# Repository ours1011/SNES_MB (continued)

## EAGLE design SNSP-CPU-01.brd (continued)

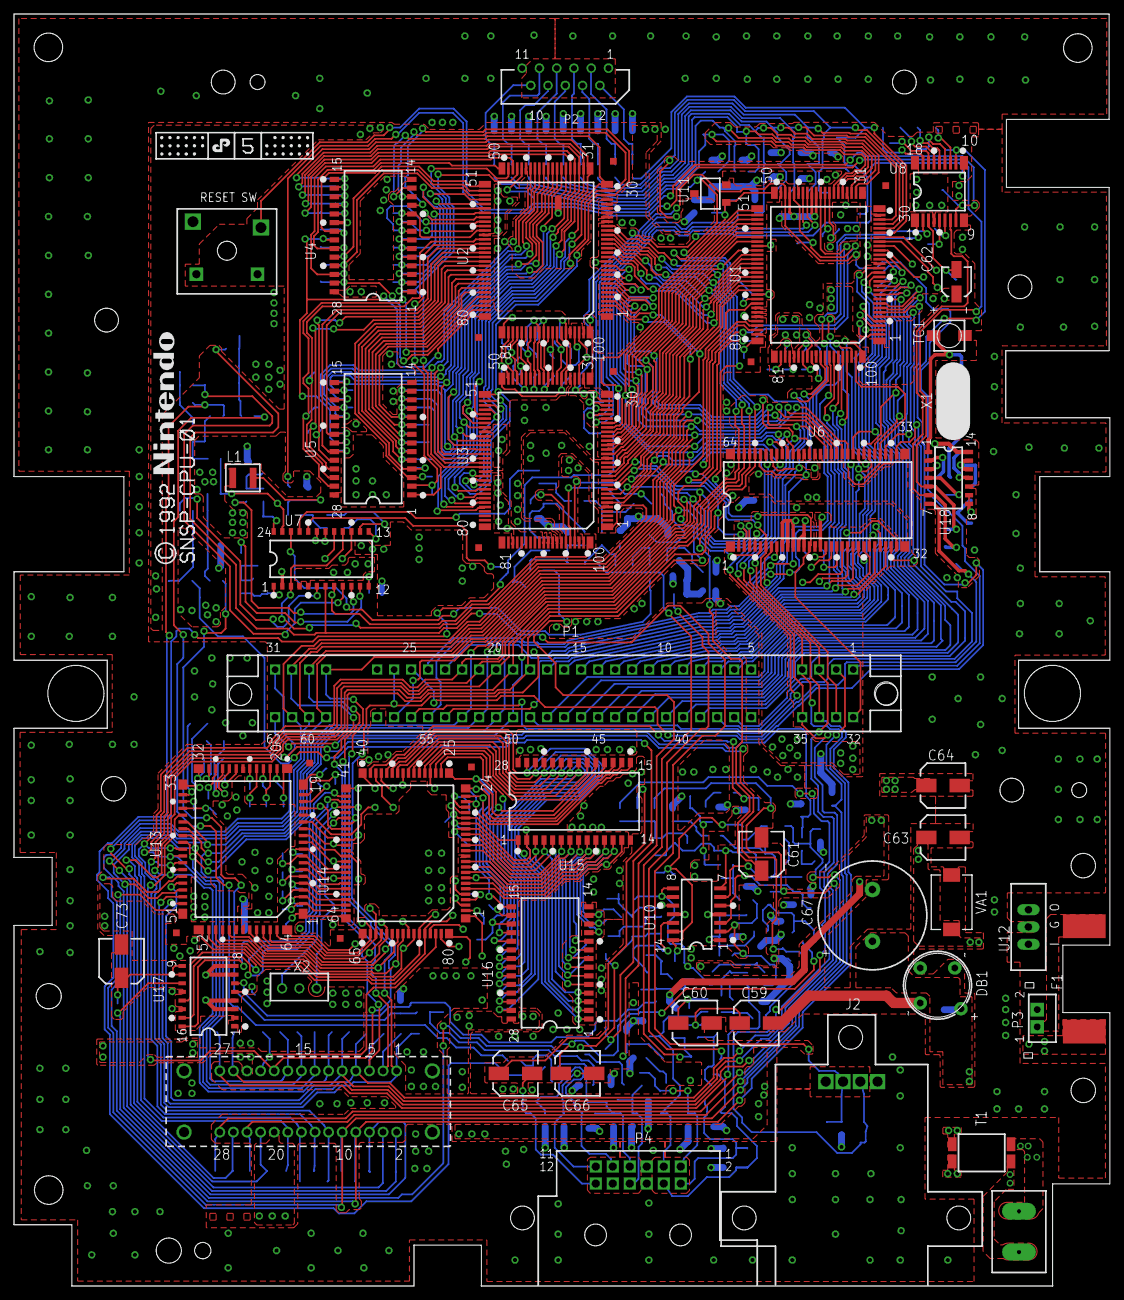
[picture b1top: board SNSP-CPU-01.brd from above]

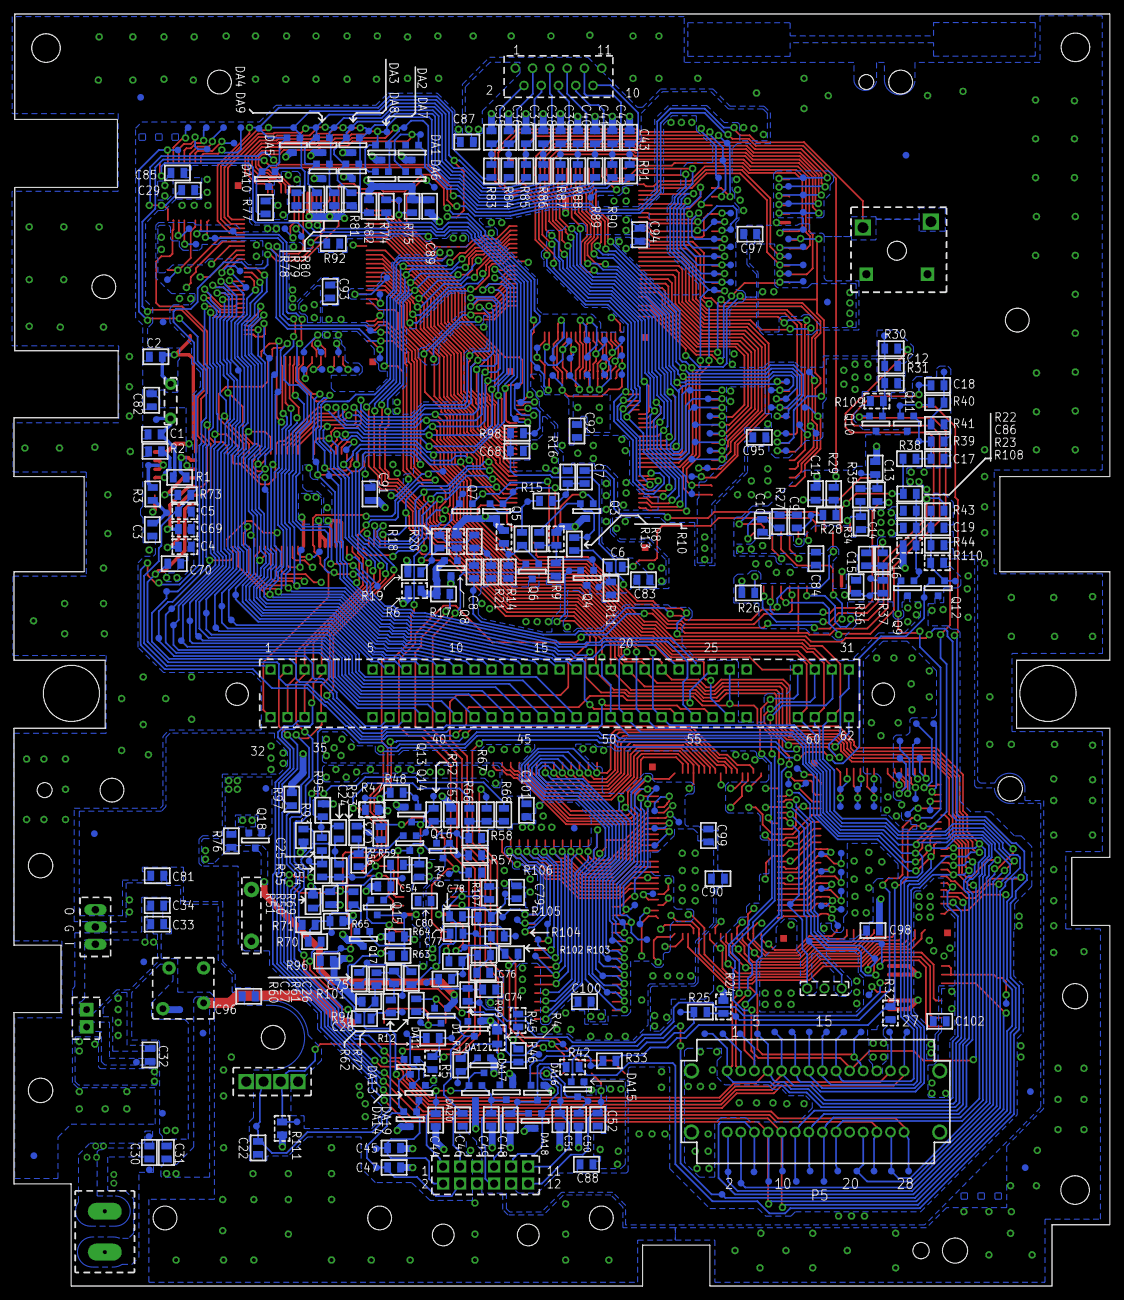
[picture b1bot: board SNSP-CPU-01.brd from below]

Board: 2 copper layers, 161.1 x 187.0 mm, 588 parts (544 on the bottom side), 374 nets.

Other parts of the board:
U$2: MB_OUTLINE
